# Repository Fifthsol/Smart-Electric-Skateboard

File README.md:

# Smart Electric Skateboard

> **FIRMWARE IS HUMAN REVIEWED, CLAUDE WRITTEN**
> WILL REWRITE BEFORE CREATING FINAL VERSION AND TESTING WITH REAL HARDWARE, DON'T USE FIRMWARE YET.

This is my PCB and CAD design for a smart electric skateboard, I designed it for the most possible modularity and to be as easily assembled as possible

## Key Features

- **XT90-S spark key**: this acts as a physical lock, completing the circuit needed for the board to power on
- **Gyroscope (MPU-6050)**: motion and orientation sensing
- **OLED display**: onboard status readout
- **Buzzer**
- **Wi-Fi + Bluetooth** (via ESP32)
- **GPS logging** (via Arduino Nano to avoid clogging ESP32) — tracks rides for eventual export to Strava
- **Regenerative braking**: logged by the ESP32
- **Hall-effect thumb throttle**: smooth, analog accel/decel control
- **Headlights**: I used a MOFSET gate to control headlights using the ESP32, the headlights are 12V and plenty bright :)

## Design Notes

The PCB is designed for easy assembly and repairability: the ESP32 and Arduino Nano mount use through-hole headers, and most other component connects through screw terminals so you don't have to resolder anything if you want to upgrade a module. A handful of parts (like the XT90 connectors) sit off-board so that wiring is easy to manage. Additionally this board is compatible with basically ever single commercially available ESC, motor, and thumb throttle costing significantly less than other commercially available "smart" skateboards with more configurability.)

You can mount the PCB using countersunk M5 bolts drilled into the main deck of your board. Reference the CAD for the positioning of these holes.

The cover that goes over can be printed and you can use velcro to create a removable cover for all electronics :)

As some of the wiring sits off board, reference my wiring diagram below :) I believe it's pretty self explanatory, use wire splice connectors where there is break points, lay everything out before hand so you cut the appropriate amount of 10 AWG wire.

## Images

here's my final two layer PCB :) you can find the KiCAD file in this repo, when ordering a PCB please only download the final gerber zip (I think I deleted the old one but still be careful)

See full assembly in the Onshape link below!

## CAD

[https://cad.onshape.com/documents/cc961e82541e14a55eb3a3aa/w/93f68d3bf484e10ac8913aa9/e/999f5a267f0d529136fe4578?renderMode=0&uiState=6a472d69a55f8813fe6f1d74 ](https://cad.onshape.com/documents/cc961e82541e14a55eb3a3aa/w/93f68d3bf484e10ac8913aa9/e/999f5a267f0d529136fe4578?renderMode=0&uiState=6a472d69a55f8813fe6f1d74) - SOURCE FILES, YOU CAN EXPORT, FOR SOME REASON ONSHAPE DOESN'T LET ME LET PUBLIC MAKE COPIES, LMK IF U NEED MORE FILES

I also added the files for the XT90S holder and key I got from thingiverse but you can also get them from the creators' thingiverse links:

https://www.thingiverse.com/thing:3755061 - DSC101
 https://www.thingiverse.com/thing:2323422 - MMANER

Additionally I'd like to credit Linny for the wonderful spark key tutorial:

https://forum.esk8.news/t/how-to-make-a-xt90-loop-key/17664 

## Hardware Recommendations

You can buy any deck you want as long as it has standard skateboard truck mounting holes (don't forget grip tape, I don't want anyone to get a concussion falling off a skateboard at 30mph)

All of the following are compatible with all of the parts:

Here's the kit I recommend: https://diyelectricskateboard.com/products/single-motor-mechanical-kit

Here's the motor I recommend: https://flipsky.net/products/6354-motor?variant=39584732020923 *make sure you buy the 8mm long shaft version, the pinion in the kit is 8mm*

Here's the ESC I recommend: https://www.amazon.com/Flipsky-Electric-Controller-Skateboard-FSESC4-20/dp/B08725X8CT?crid=3SIDHWG364BX4&dib=eyJ2IjoiMSJ9.IqoH6igNS5uoqaSPi0U1BedvgWXTG2MmrTiz3IbeygggEGuA5hgPAAYX8bJbXIFoMB16bEaBD6aKPqdNQPnGbr8ioB8Tdrru8ZNjyuO4UhzOalCiTvk_JVJ_Lxj0zglkbMqWADbCturR1eBblw_qSCXh0UQposV203Uq_D-tWq-mQEDJuYN1ny7OWe27NWZRroTPX34m-Ez5RlyCnL1I8tUvgz6dJJQ4FC1nw_zgHt5CUaAWrCW-psdJZAHDuAjBaQKz6eAdM194SUU266oIVdS7h7u9ZzuQsU9zRhYBSks.9GCl_Hz-my6_k1dOwJ4J5hVFeGhrBCk26F7K8-cv7QA&dib_tag=se&keywords=flipsky+esc&qid=1783028494&sprefix=flipsky+es%2Caps%2C216&sr=8-10

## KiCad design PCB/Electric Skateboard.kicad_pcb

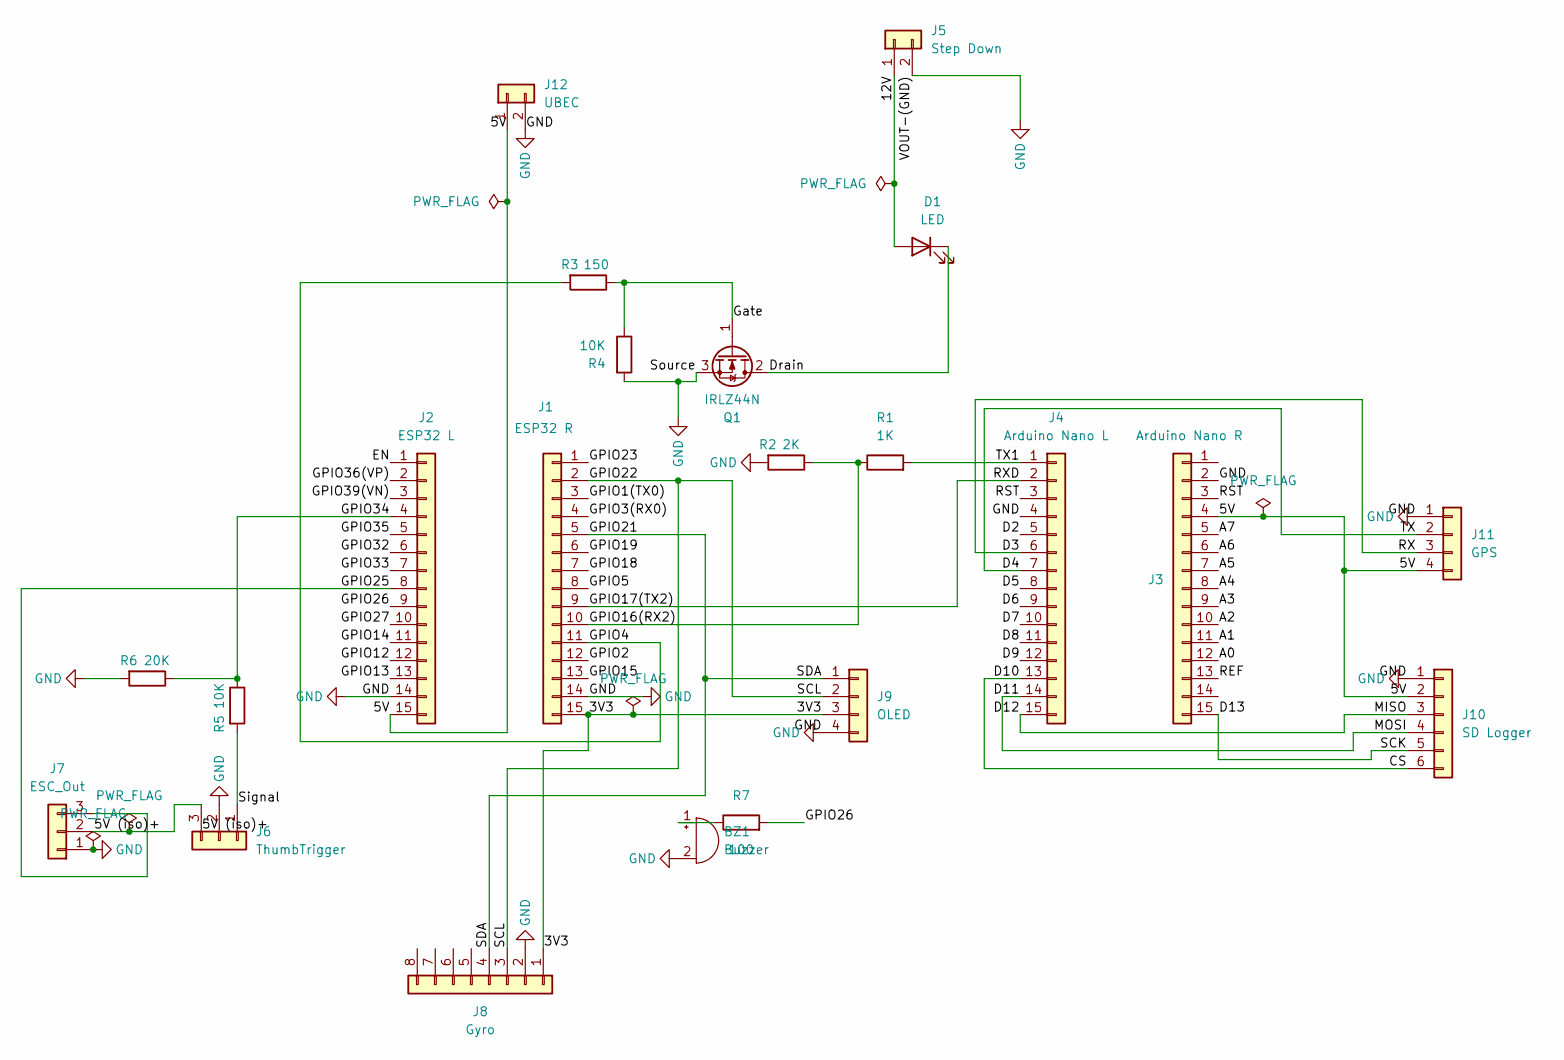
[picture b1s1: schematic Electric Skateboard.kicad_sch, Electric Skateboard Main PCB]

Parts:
BZ1: Buzzer; Buzzer_12x9.5RM7.6
D1: LED; TerminalBlock_MaiXu_MX126-5.0-02P_1x02_P5.00mm
J1: ESP32 R; PinHeader_1x15_P2.54mm_Vertical
J2: ESP32 L; PinHeader_1x15_P2.54mm_Vertical
J3: Arduino Nano R; PinHeader_1x15_P2.54mm_Vertical
J4: Arduino Nano L; PinHeader_1x15_P2.54mm_Vertical
J5: Step Down; TerminalBlock_MaiXu_MX126-5.0-02P_1x02_P5.00mm
J6: ThumbTrigger; TerminalBlock_MaiXu_MX126-5.0-03P_1x03_P5.00mm
J7: ESC_Out; TerminalBlock_MaiXu_MX126-5.0-03P_1x03_P5.00mm
J8: Gyro; PinHeader_1x08_P2.54mm_Vertical
J9: OLED; TerminalBlock_MaiXu_MX126-5.0-04P_1x04_P5.00mm
J10: SD Logger; TerminalBlock_MaiXu_MX126-5.0-06P_1x06_P5.00mm
J11: GPS; TerminalBlock_MaiXu_MX126-5.0-04P_1x04_P5.00mm
J12: UBEC; TerminalBlock_MaiXu_MX126-5.0-02P_1x02_P5.00mm
Q1: IRLZ44N; TO-220-3_Vertical
R1: 1K; R_Axial_DIN0207_L6.3mm_D2.5mm_P10.16mm_Horizontal
R2: 2K; R_Axial_DIN0207_L6.3mm_D2.5mm_P10.16mm_Horizontal
R3: 150; R_Axial_DIN0207_L6.3mm_D2.5mm_P10.16mm_Horizontal
R4, R5: 10K; R_Axial_DIN0207_L6.3mm_D2.5mm_P10.16mm_Horizontal
R6: 20K; R_Axial_DIN0207_L6.3mm_D2.5mm_P10.16mm_Horizontal
R7: 100; R_Axial_DIN0207_L6.3mm_D2.5mm_P10.16mm_Horizontal

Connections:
/3V3: J1.15, J8.1, J9.3
/5V: J2.15, J3.4, J10.2, J11.4, J12.1
/5V (iso)+: J6.3, J7.2
/12V: D1.2 (A), J5.1
/<NO NET>: J1.1, J3.3, J4.3
/A0: J3.12
/A1: J3.11
/A2: J3.10
/A3: J3.9
/A4: J3.8
/A5: J3.7
/A6: J3.6
/A7: J3.5
/CS: J4.13, J10.6
/D2: J4.5
/D3: J4.6, J11.3
/D4: J4.7, J11.2
/D5: J4.8
/D6: J4.9
/D7: J4.10
/D8: J4.11
/D9: J4.12
/D11: J4.14, J10.4
/D12: J4.15, J10.3
/D13: J3.15, J10.5
/Drain: D1.1 (K), Q1.2 (D)
/EN: J2.1
/GPIO1(TX0): J1.3
/GPIO2: J1.12
/GPIO3(RX0): J1.4
/GPIO4: J1.11, R3.2
/GPIO5: J1.8
/GPIO12: J2.12
/GPIO13: J2.13
/GPIO14: J2.11
/GPIO15: J1.13
/GPIO16(RX2): J1.10, R1.1, R2.1
/GPIO17(TX2): J1.9, J4.2
/GPIO18: J1.7
/GPIO19: J1.6
/GPIO21: J1.5, J8.4, J9.1
/GPIO22: J1.2, J8.3, J9.2
/GPIO25: J2.8, J7.3
/GPIO26: J2.9, R7.2
/GPIO27: J2.10
/GPIO32: J2.6
/GPIO33: J2.7
/GPIO34: J2.4, R5.1, R6.1
/GPIO35: J2.5
/GPIO36(VP): J2.2
/GPIO39(VN): J2.3
/Gate: Q1.1 (G), R3.1, R4.1
/REF: J3.13
/Signal: J6.1, R5.2
/TX1: J4.1, R1.2
GND: BZ1.2 (-), J1.14, J2.14, J3.2, J4.4, J5.2, J6.2, J7.1, J8.2, J9.4, J10.1, J11.1, J12.2, Q1.3 (S), R2.2, R4.2, R6.2
unnamed: BZ1.1 (+), R7.1

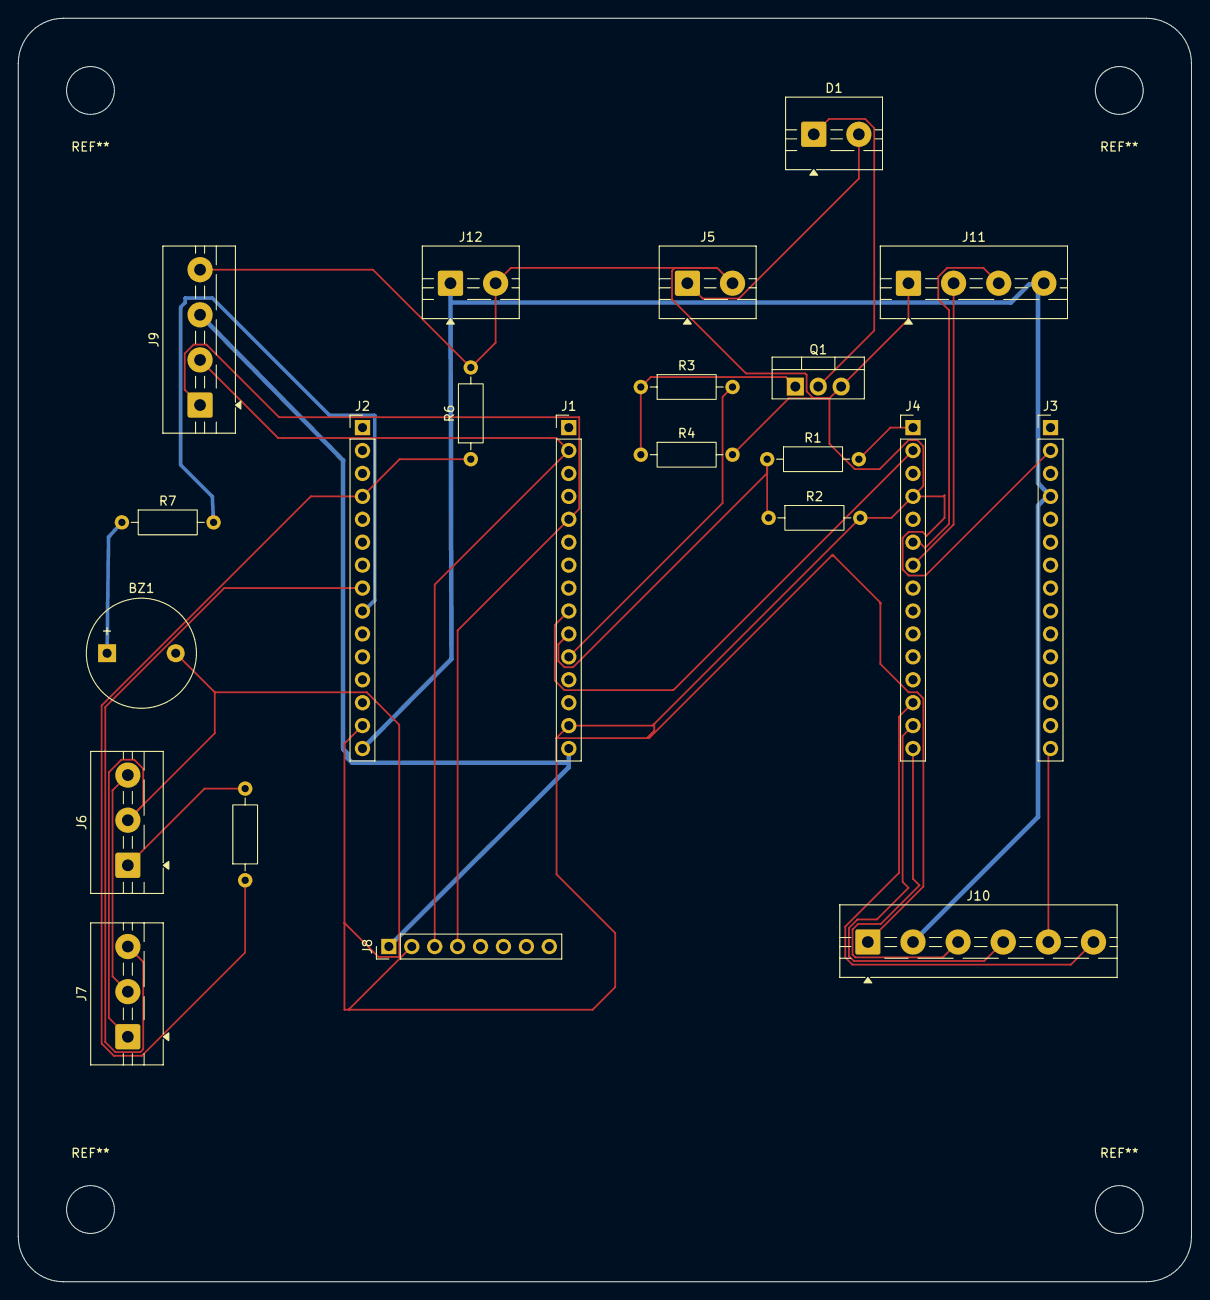
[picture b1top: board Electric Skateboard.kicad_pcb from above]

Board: 2 copper layers, 130.0 x 140.0 mm, 22 parts (0 on the bottom side), 25 nets.
